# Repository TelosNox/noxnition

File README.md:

# Feuerwerk Zündmodul + Android App
Selbstbauprojekt für Funkzündmodule

## Zielgruppe
Das Projekt richtet sich an interessierte Privatmenschen mit technischen Kenntnissen, die gerne elektrisch ihr Silvesterfeuerwerk zünden wollen.
Man sollte wissen, wie man grundsätzlich einen Schaltplan liest und wie man an Bauteilen die passenden Pins erkennt (Datenblatt). Und man sollte mit dem Lötkolben umgehen können.

Dieses Projekt richtet sich NICHT an Profis. Wer etwas für professionelle Einsatzzwecke sucht, ist hier leider falsch.
Dennoch darf natürlich gerne reingeschaut werden.

## Eckdaten
#### Zündmodul
- Funkzündmodul mit n x 8 Kanälen
- Manuelle Scharfschaltung
- Elektrische Scharfschaltung
- Durchgangsprüfung der Zünder
- Zündspannung 12V max 7A, Prüfstrom 1,2mA
- Kommunikation über WiFi (WPA gesichert)
- Einfache API über HTTP
#### Android App
- Automatische suche von Modulen
- Direkte Einzelbedienung (Scharfschalten, Durchgangsprüfung, Zündung)
- Feuerwerksplanung mit virtuellen Kanälen (Zusammenfassung mehrerer Kanäle auch unterschiedlicher Module unter einem Namen)
- Ablaufplanung mit Zeitverzögerungen (Sekundenbereich)
- Semiautomatisches Schießen des Feuerwerks

## Motivation
Das Projekt entstand durch mehrere Faktoren. Einerseits war ich gerade für den Kettenheizöler Noxmatic mit dem NodeMCU am experimentieren, andererseits hatte ich gerade ein Silvester hinter mir, an dem wir viele Batterien hatte aber diese manuell zündeten.
Ich hatte die Nase voll vom hin und herlaufen und den Pausen dazwischen. Ich hatte Bock darauf, mein Feuerwerk mal elektisch zu zünden. Keinen Bock hingegen hatte ich daruf, für eine kleine 4 Kanal China Zündanlage schon mindestens 40€ hinzulegen zumal ich ja wusste, wie billig man schon den NodeMCU und die als Treiber nötigen Komponenten bekommt.
Ich hatte auch Bock darauf, sowas mal selbst zu entwickeln, also brachte ich die Idee im Feuerwerk Forum (www.feuerwerk-forum.de) mal zur Sprache und bekam dort viele hilfreiche Ratschläge von Mitgliedern, die elektrotechnisch noch einiges fitter sind, als ich. Für diese Hilfe bin ich sehr Dankbar, denn bei einer Zündanlage geht es auch um Sicherheit und da sollte man nicht am falschen Ende sparen.

## Die Idee
Ich wollte eine Zündanlage für den Selbstbau entwickeln, die möglichst einfach und möglichst günstig nachzubauen und zu bedienen ist. Dabei sollte sie möglichst offen für Erweiterungen sein.
Kommuniziert wird über WLAN, das Protokoll ist HTTP und als Fernsteuerung dient einfach ein beliebiges Android Gerät (hat eigentlich jeder zu Hause).

## Entstehung des Zündmoduls
Ursprünglicher Plan war, dass ein Zündmodul genau 8 Kanäle + eine elektrische Scharfschaltung hat. Der NodeMCU hat genau 9 schaltbare digitale Ausgänge, das reicht für die 8 Kanäle sowie den einen Ausgang für die Scharfschaltung.
An die Ausgänge einfach direkt MosFet als Low Side Schalter dran (ohne weitere Beschaltung) und die Scharfschaltung ebenso als Low Side Schalter für die Gesamtmasse.

Hat so leider nicht funktioniert.
Also gab es folgende Schritte, die zum aktuellen Schaltplan geführt haben.

#### MosFet ordentlich beschalten
Da hier pyrotechnische Gegenstände zum Einsatz kommen, von denen eine gewisse Gefahr ausgeht, muss die Treiberschaltung ordentlich sein. Daher war es gegeben, die MosFet mit einer ordentlichen Schaltung zu versehen.

#### Scharfschaltung mit Low Side Schalter geht nicht
Man kann nicht die Masse eines Low Side MosFet wieder als Busspannung für einen anderen Low Side MosFet verwenden. Das funktioniert so einfach nicht. Also musste eine High Side Schaltung mit einem P-MosFet her. Damit der NodeMCU das aber korret ansteuern kann, wird trotzdem noch ein Low Side gebraucht. Somit war ein zusätzlicher MosFet und Widerstände nötig.
Da P-MosFet keinen so tollen Innenwiderstand wie N-MosFet haben ist der zusätzliche MosFet auch leider nicht ganz so billig.

#### Der NodeMCU zappelt
Leider leider hat so ein NodeMCU 3 Pins, die beim booten kurz zappeln. Die elektrische Scharfschaltung verhindert, dass beim Einschalten irgendwas passieren kann. Wenn allerdings Scharf geschalten ist und dann der Controller einen Reset durchführt, zappeln die Pins und es liegt kurz Zündspannung an.
Meine A-Zünder haben beim Versuch nicht ausgelöst. Trotzdem war das zu unsicher.
Da keine weiteren Pins verfügbar waren und eine Anlage mit nur 5 Kanälen wenig Sinn macht, wurde das Schieberegister hinzugefügt. Somit war das n x 8 Modul geboren, denn die Schaltung erlaubt es jetzt beliebig viele Schieberegister hintereinander zu reihen und so ein beliebiges vielfaches von 8 Kanälen umzusetzen.
Ich selbst habe mir Module mit 8 und 16 Kanälen gebaut.

#### Zu viel Strom!
Da so ein Zünder quasi einen Kurzschluss darstellt und auch Parallelschaltungen von Zündern funktionieren sollen ohne dass Akku oder MosFet abrauchen, wurde noch eine Strombegrenzung eingeführt. Das ist ein simpler großer 10W Draht Keramik Lastwiderstand mit 1,8Ohm. Somit liegt der maximal mögliche Strom bei nominal 12V Spannung (real dann knapp 13) bei ca. 7A.
Natürlich kann das nicht als Dauerstrom betrieben werden. Der P-MosFet erhitzt sich. Für Dauerstrom bräuchte er eine Kühlung.
Der Lastwiderstand ist mit den so anliegenden gut 70W ebenso überfordert, kann das über kurze Zeiträume aber über Wärme abpuffern.
Wen man ganz Safe gehen will, kann man den Widerstand auf 5,6Ohm erhöhen. Damit liegt der Strom bei 2,3A und die Leistung bei 25W. Größere Parallelschaltungen könnten dann aber schwierig werden.

Ergänzt man das alles jetzt noch mit der Spannungsmessung und ein paar Schaltern sowie LEDs und Terminals, kommt man zu dem Schaltplan, der schließlich entstanden ist und umgesetzt wurde.

## Aufbau des Zündmoduls
### Bauteile (Basis)
Die folgenden Bauteile sind nötig, um überhaupt die Grundlage des Moduls zu bilden. Sie bleiben immer gleich, egal wieviele Kanäle man umsetzt.
- 1x NodeMCU V3 (Lolin)
- 2x Kippschalter (am besten unterschiedlich, so dass man Hauptschalter von Zündschalter unterscheiden kann)
- 1x Draht Keramik Lastwiderstand 1,8Ohm 10Watt (R1)
- 1x IRF9540N (Elektrische Scharfschaltung)
- 1x IRF3708 (Elektrische Scharfschaltung)
- 5x R 10k
- 1x R 4,7k
- 2x R 1k
- 1x C 100nF
- 3x LED 12V (Rot, Gelb, Grün)
- 1x Bleiakku 12v (z.B. Ultracell UL1.3-12 den verwende ich)
- 2x Kabelschuhe zum Anschluss des Akkus
- Ausreichend Draht zum verbinden (Mehrfarbig ist Hilfreich) - 0,5mm Querschnitt für Haupt und Zündleitungen, Steuerleitungen dürfen kleiner sein
- Flexible Litze für den Akku und sonstige bewegliche Teile (es ist praktisch, wenn man die Platine aus dem Gehäuse nehmen kann, um bei Bedarf Software aufzuspielen)

### Bauteile je 8 Kanäle
Die folgenden Bauteile sind nötig, um jeweils 8 Kanäle umzusetzen. Diese kann man beliebig vervielfachen.
- 1x 74HC595 (Schieberegister)
- 8x R 100
- 8x R 10k
- 8x Anschlussterminal (Lautsprecherklemmen z.B.)

Will man 16 Kanäle umsetzen, dann braucht man das einfach doppelt, bei 24 Kanäle 3x etc..

### Schaltplan Erläuterung
Hier findet ihr den [Schaltplan](Hardware/KiCad/Zündanalage_Neu/Schematic.pdf)

Ich bin kein Profi, was KiCad angeht, daher ist sicherlich nicht alles optimal.
Für die Schalter hatte ich kein Bauteil gefunden. Daher die gestrichelte Linie und den entprechenden Namen (Hauptschalter, Zündschalter).
Verbunden ist bei Überkreuzungen nur das, was einen Punkt hat.
Die Schieberegister hatten keinen Pin für Vcc, daher ist da ein extra Punkt eingezeichnet und benannt. Das muss an den entsprechenden Pin angeschlossen werden.
Der Schaltplan zeigt den Aufbau für 16 Kanäle. Will man nur 8 Kanäle umsetzen, so lässt man das rechte Schieberegister und alle daran angeschlossenen Treiber einfach weg. Die Leitung, die auf Pin 9 ankommt, muss dann stattdessen beim linken Schieberegister auf Pin 9 angeschlossen werden.
Warum?
Die Schieberegister sind seriell durchgeschleift, indem der serielle Ausgang (Pin 9) des ersten Registers an den Eingang (Pin 14) des nächsten Registers geht. Das LETZTE Register geht dann wieder zurück zum Controller. Will man noch mehr Schieberegister nutzen, so fügt man sie nach diesem Schema einfach zwischen die beiden Register des Schaltplans ein.
Alle anderen Datenleitungen sind als Bus ausgeführt. An jedem Register kommt das selbe an.
Dadurch, dass das letzte Register (bei 8 Kanälen ist das auch das Erste) diesen Ausgang an den Controller zurückgibt, kann der Controller zählen, wieviele Kanäle vorhanden sind. Mit diesem Trick funktioniert die selbe Software mit beliebig vielen Registern. Es wäre sogar möglich, ein einzelnes größeres Register zu verwenden, solange die gleichen Eigenschaften vorliegen.

### Aufbau
Für das Zündmodul gibt es keine vorgefertigte Platine. Es bietet sich an, die Bauteile auf Lochraster zu löten.
Zu aller erst sollte man sich Gedanken machen, wo und wie man alle Bauteile platziert.
Generelle Strategie: An einem Ende Controller und Basisbeschaltung zusammen. Dann mittig Schieberegister und am anderen Ende die MosFet mit Widerstanden.

Wenn man Schritt für Schritt vorgehen will, lötet man zunächst nur den Basisaufbau (nicht übersehen, dass die LED vom Zündschalter auf Masse geht, die Leitung läuft durch die ganzen Treiber). Die rote LED ist für den Hauptschalter gedacht, die gelbe für den Zündkreisschalter und die Grüne zeigt Zündbereitschaft an. Wer möchte mann auch die grüne LED als EIN/AUS nutzen und die rote LED als Warnfarbe für Zündbereitschaft. Die Anleitung geht davon aus, dass Rot für EIN/AUS benutzt wird und beschreibt entsprechend.
Temporär muss man jetzt D2 und D3 (über den vorhandenen 1k Widerstand) überbrücken. Dann kann man Software aufspielen und testen. Die LEDs sollten schon korrekt reagieren (Power LED beim Hauptschalter, Zünd LED beim Zündschalter und die Zündleitungs LED bei Scharfschaltung). Anmerkung: Die Zündleitungs LED leuchtet bei eingeschalteter Power LED schwach. Das ist normal, da Prüfspannung auf der Zündleitung anliegt.
Ebenso sollte die Spannungsanzeige in der App funktionieren (etwa Nennspannung bei eingeschalteter Zündung und ansonsten 2-3V).

Falls an dieser Stelle irgendwas nicht wie beschrieben geht: Fehler suchen.

Anschließend ist es praktisch die MosFet jeweils in Reihen zu setzen, so dass man die Massebeine direkt aufeinander löten kann. Aber Platz lassen, da müssen noch Widerstände hin. Die ebenfalls einlöten, so dass nur noch das Schaltsignal am R100 Widerstand fehlt und der Ausgang zum Anschlussterminal.
Zuletzt die Schieberegister platzieren und verlöten. Nicht vergessen: Die Brücke zwischen D2 und D3 aufmachen und an den Registern korrekt anschließen.

## Bedienung des Zündmoduls
Am Zündmodul gibt es nur 2 Schalter und 3 Leds.
Der Zündkreisschalter sollte beim Einschalten immer ausgeschalten sein (Sicherheit). Dann den Hauptschalter umlegen.
Die rote LED leuchtet, um den Betriebszustand EIN anzuzeigen. Die grüne Zündkreis LED leuchtet schwach (das lässt sich nicht verhindern bzw. wäre nur mit zusätzlichem Aufwand lösbar), das ist normal.
Jetzt ist das Modul Betriebsbereit. Der Zündkreisschalter wird erst dann umgelegt, wenn alle Zünder fertig angeschlossen sind und man sich vergewissert hat, dass die elektrische Scharfschaltung AUS ist (mittels App). Auch die Durchgangsprüfung sollte man sicherheitshalber immer mit ausgeschaltenem Zündkreisschalter machen.

### Konfiguration
Das Modul versucht sich ca. 30sec lang automatisch mit dem konfigurierten WiFi zu verbinden (initial ist noch nichts konfiguriert). Findet es kein passendes Netz, wird es automatisch selbst zum AccessPoint. Per default gelten folgende Daten:
- ssid = "noxnition"
- passwort = "noxnition"
- ip = 192.168.0.128
Das kann im ino Script vorm Einspielen der Software geändert werden.

Nun verbindet man sich mit dem Modul über WiFi, so kann man im Browser einfach die IP des Moduls aufrufen. Es erscheint eine kleine Webseite, mit der das Modul konfiguriert werden kann.
Einzustellen sind:
- Modulname
- SSID
- Passwort

SSID und Passwort beziehen sich hier auf das WiFi, zu dem das Modul sich verbinden soll. Der Modulname MUSS bei Verwendung der App eindeutig sind. Wenn mehrere Module verwendet werden, unterscheidet die App sie anhand ihres Namens.

### Kommunikation
Ist das Modul konfiguriert und loggt sich in ein WiFi ein, so schaltet es in den Bereitschaftsmodus. Jetzt können über HTTP die Funktionen aufgerufen werden.

Allgemein werden alle Aktionen über HTTP GET gesteuert. Für das Feuern eines Kanals wird der Kanal als Parameter übergeben.
Die Antwort ist immer ein simpler Text in Form von Properties.

#### Status
Mit einem HPPT GET und dem Pfad "state" wird der Status abgerufen. Beispiel: `GET http://192.168.0.128/state`
Als Antwort erhält man Spannung und Zündzustand.
- voltage=12.6
- a=1

#### Zündbereitschaft EIN
Mit einem HPPT GET und dem Pfad "arm" wird Zündbereitschaft aktiviert. Beispiel: `GET http://192.168.0.128/arm`
Als Antwort erhält man operation=1 einen Misserfolg gibt es hier nicht.

#### Zündbereitschaft AUS
Mit einem HPPT GET und dem Pfad "disarm" wird Zündbereitschaft aktiviert. Beispiel: `GET http://192.168.0.128/disarm`
Als Antwort erhält man operation=1 einen Misserfolg gibt es hier nicht.

#### Kanal zünden
Mit einem HTTP GET und dem Pfad "fire" wird ein Kanel gezündet. Als Parameter "channel" ist die Kanalnummer zu übergeben. Beispiel: `GET http://192.168.0.128/fire?channel=6`
Als Antwort erhält man Bestätigung und den gefeuerten Kanal
- operation=1
- channel=6

#### Durchgangsprüfung durchführen
Mit einem HTTP GET und dem Pfad "check" wird auf allen Kanälen auf Durchgang geprüft. Beispiel: `GET http://192.168.0.128/check`
Die Anlage stellt nun sicher, dass sie NICHT Zündbereit ist und prüft zusätzlich die anliegende Zündspannung. Geht hier etwas schief, so kommt operation=0 zurück, um den Fehler anzuzeigen. Ansonsten kommt operation=1 und für jeden Kanal die Info, ob er Durchgang hat
- operation=1
- c1=0
- c2=1
- c3=1
- etc...

#### Modulkonfiguraton abfragen
Mit einem HPPT GET und dem Pfad "getConfig" wird die Modulkonfiguration abgefragt. Beispiel: `GET http://192.168.0.128/getConfig`
Als Antwort erhält man den Modulnamen und die Anzahl Kanäle
- name=Fiffi
- channels=16

#### Modul finden
Da die Module über DHCP eine IP bekommen und diese dem Sender somit nicht zwingend bekannt ist, können Module per Broadcast gefunden werden. Jedes Modul reagiert auf UDP Broadcast und sendet als Antwort an den Absender ein UDP Paket mit einer Antwort, wie bei den HTTP Requests. Sie enthält Modulname, Kanäle und den Inhalt der Broadcast Nachricht (zur Identifikation des Requests, wenn zyklisch gepollt wird)-
- name=Fiffi
- channels=16
- request=broadcast135213 (in der Regel sendet man irgend einen Zufallswert oder zählt sequenziell hoch)

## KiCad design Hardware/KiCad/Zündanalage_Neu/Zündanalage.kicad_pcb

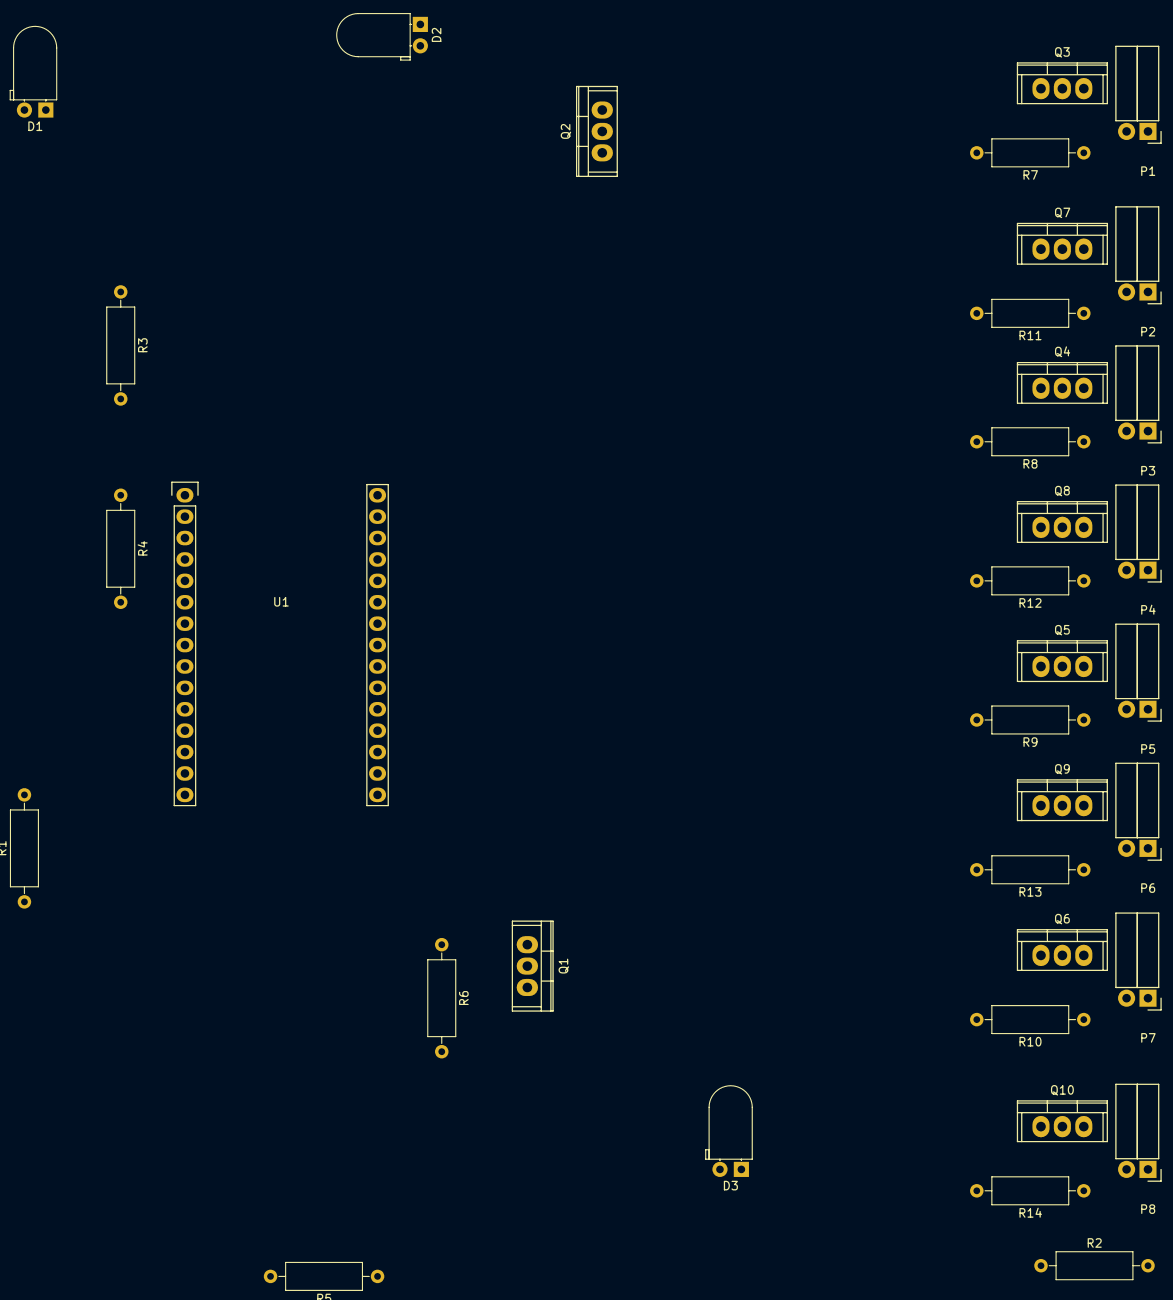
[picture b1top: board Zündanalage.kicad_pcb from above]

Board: 2 copper layers, 36 parts (0 on the bottom side), 24 nets, no tracks yet.

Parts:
D1: LED 12v Power; LED_D5.0mm_Horicontal_O1.27mm
D2: LED 12v Zündschalter; LED_D5.0mm_Horicontal_O1.27mm
D3: LED 12v Zündleitung; LED_D5.0mm_Horicontal_O1.27mm
P1: Zünder1; Socket_Strip_Angled_1x02
P2: Zünder2; Socket_Strip_Angled_1x02
P3: Zünder3; Socket_Strip_Angled_1x02
P4: Zünder4; Socket_Strip_Angled_1x02
P5: Zünder5; Socket_Strip_Angled_1x02
P6: Zünder6; Socket_Strip_Angled_1x02
P7: Zünder7; Socket_Strip_Angled_1x02
P8: Zünder8; Socket_Strip_Angled_1x02
Q1, Q3, Q4, Q5, Q6, Q7, Q8, Q9, Q10: IRF3708; TO-220
Q2: IRF9540N; TO-220
R1: 1,8; R_Axial_DIN0309_L9.0mm_D3.2mm_P12.70mm_Horizontal
R2, R5, R6, R7, R8, R9, R10, R11, R12, R13, R14: 10k; R_Axial_DIN0309_L9.0mm_D3.2mm_P12.70mm_Horizontal
R3: 4,7k; R_Axial_DIN0309_L9.0mm_D3.2mm_P12.70mm_Horizontal
R4: 1k; R_Axial_DIN0309_L9.0mm_D3.2mm_P12.70mm_Horizontal
U1: NodeMCU_Amica_R2

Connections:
GND: D1.1, D2.1, D3.1, Q1.3, Q3.3, Q4.3, Q5.3, Q6.3, Q7.3, Q8.3, Q9.3, Q10.3, R4.2, R6.2, R7.1, R8.1, R9.1, R10.1, R11.1, R12.1, R13.1, R14.1, U1.14
unnamed: D1.2, R1.2, U1.15
unnamed: D2.2, Q2.3
unnamed: D3.2, P1.1, P2.1, P3.1, P4.1, P5.1, P6.1, P7.1, P8.1, Q2.2, R2.2, R3.1
unnamed: P1.2, Q3.2
unnamed: P2.2, Q7.2
unnamed: P3.2, Q4.2
unnamed: P4.2, Q8.2
unnamed: P5.2, Q5.2
unnamed: P6.2, Q9.2
unnamed: P7.2, Q6.2
unnamed: P8.2, Q10.2
unnamed: Q1.1, R6.1, U1.22
unnamed: Q1.2, Q2.1, R5.1
unnamed: Q3.1, R7.2, U1.29
unnamed: Q4.1, R8.2, U1.21
unnamed: Q5.1, R9.2, U1.23
unnamed: Q6.1, R10.2, U1.27
unnamed: Q7.1, R11.2, U1.28
unnamed: Q8.1, R12.2, U1.20
unnamed: Q9.1, R13.2, U1.30
unnamed: Q10.1, R14.2, U1.26
unnamed: R1.1, R2.1, R5.2
unnamed: R3.2, R4.1, U1.1

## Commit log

2017-03-20 Initial publish
2017-03-20 Add KiCad sketches
2017-12-23 Broadcast Fix + Semi automatic mode
    - Some Code improvements have been done
    - Broadcast with tethering has been fixed
    - Automatic mode has been replaced by semi automatic mode
2017-12-23 Broadcast fix + Semi automatic mode
    commit missing files
2018-01-03 Rework persistence, some UI and Bugfix
    - Persistence now uses JSON, so it is easier to change/enhance
    - Planned Firework is not accessed by button anymore. Instead the main
    screen is swiped
    - Add capability to retry ignition in planned firework if ignition
    command is not confirmed
2018-01-03 Restructure packages
2018-01-05 Rework Firework planning
    Introduced Fire Trigger Groups which can assign multiple channels to one
    single item.
    Firework planning is currently broken. No Fire Actions can be assigned
    because in future they will be based on the new Trigger Groups
2018-01-06 Rework firework planning
    Deny duplicate selection of already used channels for fire triggers
2018-01-06 Add Schematic as pdf
2018-01-07 Rework firework planning
    Adapt Fire Actions and Fire Action planning to new Fire Trigger Approach
2018-01-07 Rework firework planning
    Adapt execution of planned firework to be able to use the new Fire
    Triggers as base
2018-01-07 Improve progress of planned firework execution
    Next fire action counts down remaining seconds of entered delay
2018-01-07 Check if all needed modules for planned firework are online
2018-01-07 Improve planned firework execution
    Check if all needed channels are connected
2018-01-07 Improve planned firework execution
    Check if all planned fire actions have triggers with channels assigned
2018-01-07 Improve planned firework execution
    Set all required modules into armed state and check if the state has
    been switched
2018-01-14 Fix issue #4
    Deny execute firework if no actions exist
2018-01-14 Fix issue #5
    Sort triggergroups by name
2018-01-14 Fix issue #6
    Don't show already assigned trigger groups for fire action creation
2018-01-14 Fix wrong instantiation of fragments
    Fragments caused the app to crash if the app has been restored due to
    wrong usage
2019-01-11 Fix broken broadcast
    Enforce ipv4 network adapter for broadcast
2019-01-12 Improve Communication Structure
    Remove own created threads in communication and use async task instead.
    Calculate average ping of modules instead of single value and allow
    longer connection timeout.
